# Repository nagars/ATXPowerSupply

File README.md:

# ATXPowerSupply (Completed 05/19/2017)

# Important Note
**This was the first PCB I designed. Please keep that in mind if you decide to reference this design.**

# Inspiration
Soon after graduating college while applying for jobs as an emedded systems engineer, I realised that knowing how to effectively design PCB's was a good skill to have. 
I also had some personal projects in mind that I wanted to work on to improve my skills with various MCU's. So I figured I would manufacture my own PCB designs. Most blogs recommend 
starting with EagleCAD as it has good community support and is especially popular with hobbyists. Unlike other free professional softwares, Eagle is only limited by the 
size of the board and not by the number of nets like Orcad PCB designer. 

At the time, I found an old ATX power supply lying in storage at the department of Electrical Engineering. It was leftover from some senior design project so with their permission, 
I took it. Thats when I got the idea to design a simple breakout for this board I could use with whatever projects I had lined up. 

# Table of Contents
1. Objective
2. Feature List
3. Design Breakdown
4. Issues
5. Final Comments

## Objective
The objective of the project was to learn EagleCAD as a complete new comer. It would also be an opportunity to learn about various design methodologies and considerations that
go into PCB design. Finally, I would have a good power supply breakout board.

## Feature List
- Connects to a standard 20 pin ATX power supply connector
- A standard toggle switch should be able to enable/disable the power supply
- Each power line should be broken out into a seperate 2.54mm header
- Should have an LED to indicate if power is on or not

## Design Implementation
The design is fairly simplistic. A 20 pin ATX female header is placed on one side of the board to connect to the power supply. A standard SPDT toggle switch is connected to Power Enable
pin of the ATX supply. This enables/disables the power supply. An LED is driven off the 5V power line with a current limiting resistor to indicate if power is on or not. Finally,
there are 4 power lines borken out standard 2.54mm 10 pin header:

    - 12V  32A 
    - 5V   16A
    - 3.3V 16A
    - -12V 0.3A
    
Finally, a 20 pin header is used to breakout the ground pins.

## Issues
Because all of my projects I used this supply for consumed very little power, I never experienced any issue. But looking back now in 2021, I can see quite a few areas of concern
and little use of some common PCB design practices.

1. None of the traces are thick enough to handle currents as high as 32A. In the end, the PCB should be designed for the worst case conditions. Using an [online trace width 
calculator](https://www.7pcb.com/trace-width-calculator.php) you can get a good idea of how thick your traces should be for max current. 
2. The 2.54 mm breakouts would probably melt in high current situations. 
3. I didn't use the bottom layer (Layer 16) as a mirror for the power lines. This is a common way of doubling the current carrying capacity of a single net.
4. Often to dissipate heat and improve current carrying capacity, the power lines can be turned into planes covering a larger area rather than a single trace. Connecting the planes on both layers together 
(Layer 1 and 16) using via's, assuming its a standard 2 layer board is recommended.
5. The GND plane is also only on layer 1 and not on layer 16 as well. Joining these 2 layers with via's would allow for much better current and heat dissipation. 
6. I ignored the DRC errors. DRC stands for **Design Rules Check**. You can assign rules that must be followed such as the distance if via's from the edge of the board
or the minimum trace widths. Unless your circuit has specific design requirements, I recommend sticking with the default rules or setting the design rules recommended by your manufacturer.
From personal experience I can assure you it will save you a lot of headache at some point.

## Final Comments 
There is a fundamental flaw in this project which is also the source of the issues stated above. I was using this power supply for breadboards and low power consumption applications.
There is no conceivable situation where I would require 32A of current, or even 16A or 8A. For up to 4A of current per power line, this design will do. As a result,
I didn't design it for high current applications. 

For the intent of use, this design works fine ... mostly. Common practices of using both layer 1 and 16 for traces and ground planes are good but not always necessary.
It's not great but for my very first PCB, I'm happy with it. It worked and served it's purpose.

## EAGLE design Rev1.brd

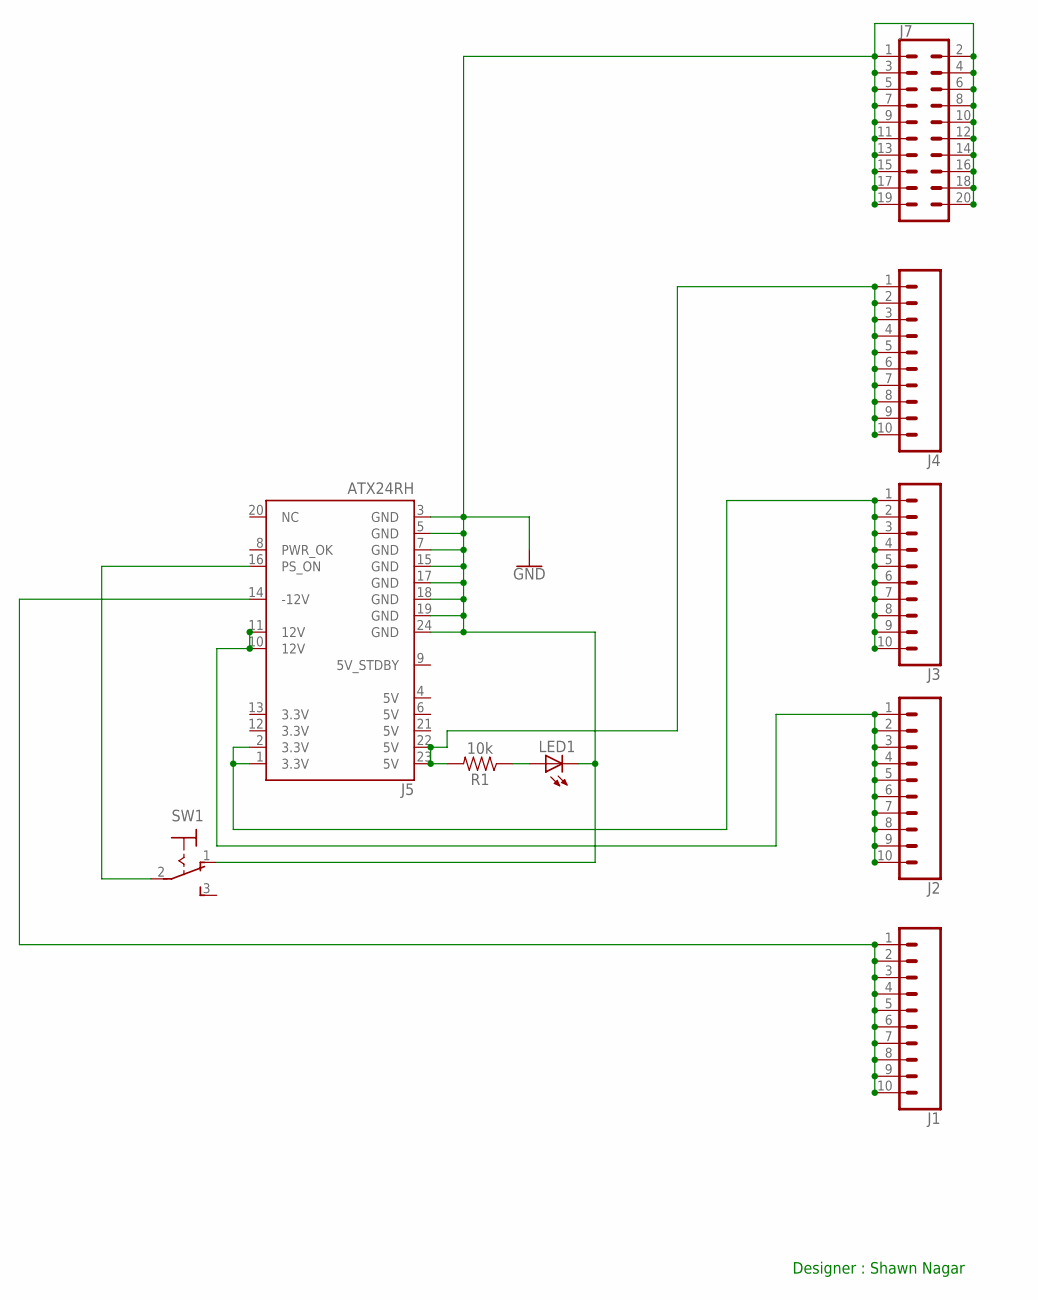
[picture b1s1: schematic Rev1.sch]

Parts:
J1, J2, J3, J4: CONN_10"; 1X10
J5: ATX24RH; ATX24_RIGHT_ANGLE
J7: CONN_10X2; 2X10
LED1: LED5MM
R1: 10k; AXIAL-0.3
SW1: 320-916

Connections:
GND: J5.3 (GND), J5.5 (GND), J5.7 (GND), J5.15 (GND), J5.17 (GND), J5.18 (GND), J5.19 (GND), J5.24 (GND), J7.1, J7.2, J7.3, J7.4, J7.5, J7.6, J7.7, J7.8, J7.9, J7.10, J7.11, J7.12, J7.13, J7.14, J7.15, J7.16, J7.17, J7.18, J7.19, J7.20, LED1.K (C), SW1.1 (O)
unnamed: J5.16 (PS_ON), SW1.2
unnamed: LED1.A, R1.P$1 (1)
unnamed: J4.1, J4.2, J4.3, J4.4, J4.5, J4.6, J4.7, J4.8, J4.9, J4.10, J5.22 (5V), J5.23 (5V), R1.P$2 (2)
unnamed: J3.1, J3.2, J3.3, J3.4, J3.5, J3.6, J3.7, J3.8, J3.9, J3.10, J5.1 (3.3V), J5.2 (3.3V)
unnamed: J2.1, J2.2, J2.3, J2.4, J2.5, J2.6, J2.7, J2.8, J2.9, J2.10, J5.10 (12V), J5.11 (12V)
unnamed: J1.1, J1.2, J1.3, J1.4, J1.5, J1.6, J1.7, J1.8, J1.9, J1.10, J5.14 (-12V)

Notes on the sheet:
Designer : Shawn Nagar

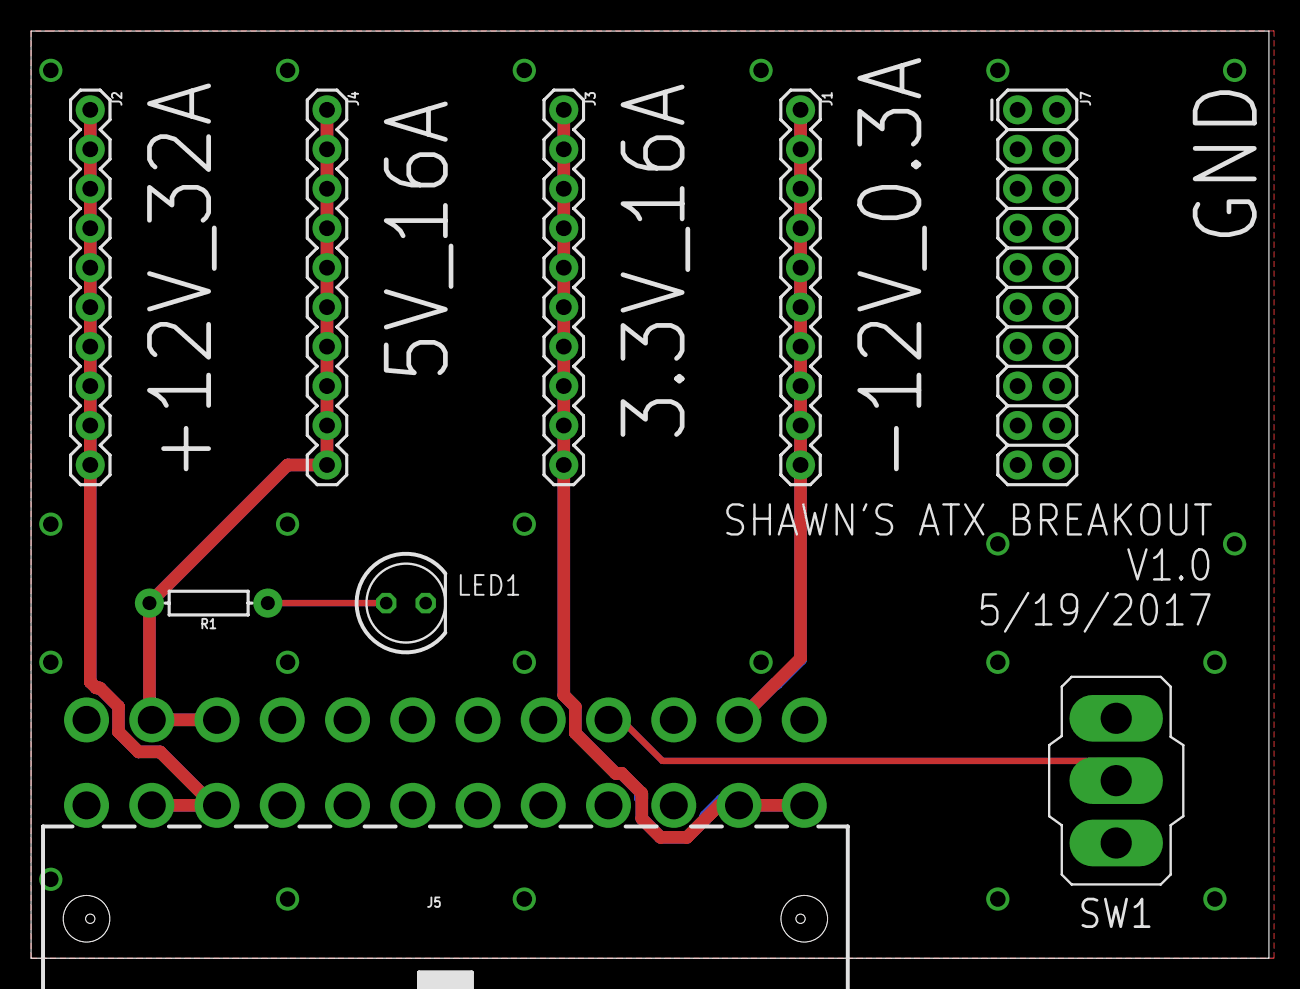
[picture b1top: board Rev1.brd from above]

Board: 2 copper layers, 79.7 x 59.7 mm, 9 parts (0 on the bottom side), 7 nets.

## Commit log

2019-06-25 Add files via upload
    My first PCB design. Made in the summer of 2018 after senior design.
2021-01-05 Cleaned up directory

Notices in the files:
parts and their libraries:
SparkFun-Connectors: Licensing: Creative Commons ShareAlike 4.0 International - https://creativecommons.org/licenses/by-sa/4.0
